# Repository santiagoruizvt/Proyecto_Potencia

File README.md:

# Proyecto_Potencia
Repositorio destinado al proyecto de la materia Electrónica de Potencia

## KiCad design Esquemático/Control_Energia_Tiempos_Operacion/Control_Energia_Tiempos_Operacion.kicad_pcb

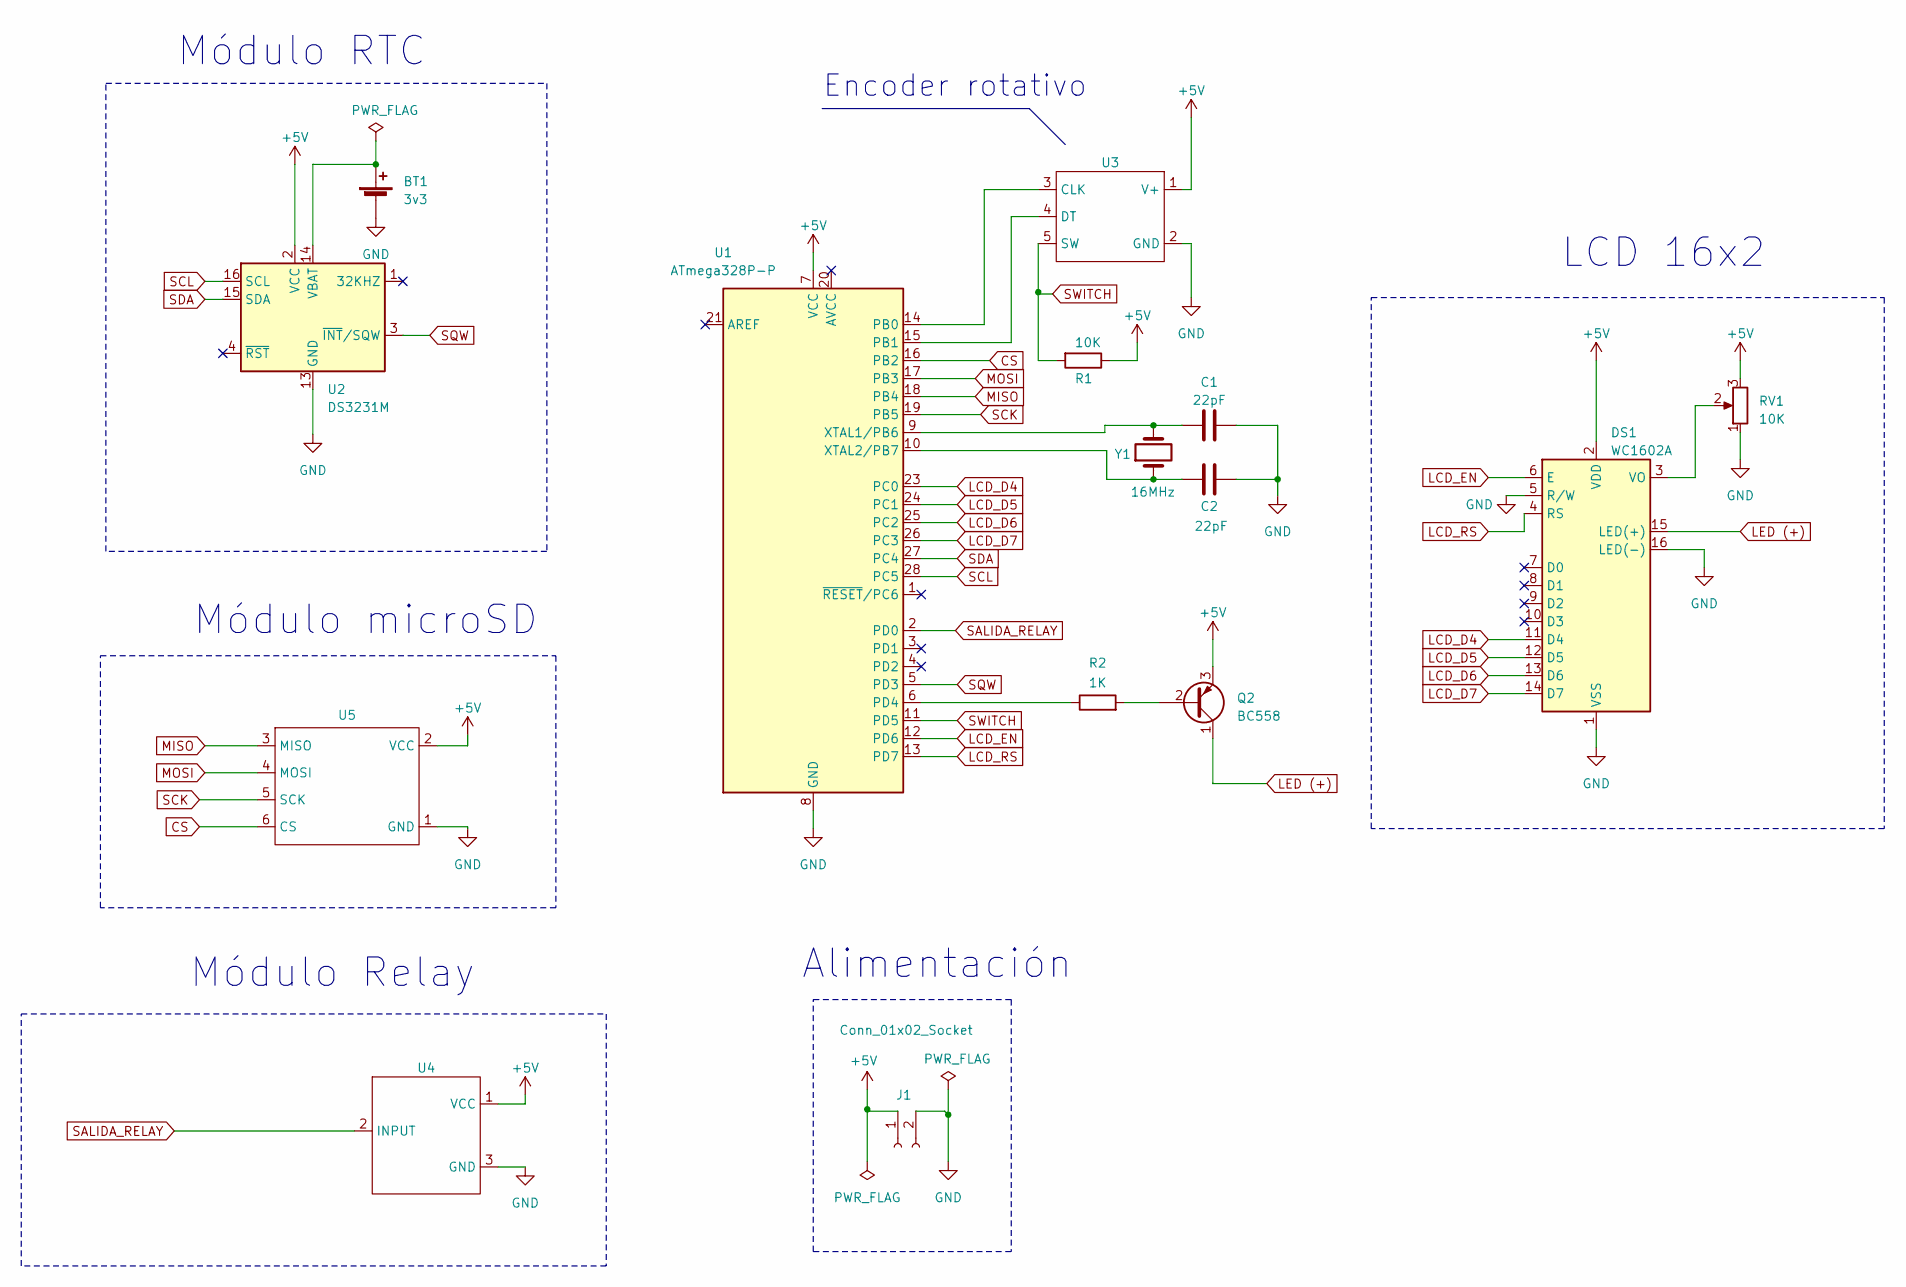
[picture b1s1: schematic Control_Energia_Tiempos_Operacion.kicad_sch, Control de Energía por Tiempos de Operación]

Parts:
BT1: 3v3
C1, C2: 22pF; C_Disc_D5.0mm_W2.5mm_P2.50mm
DS1: WC1602A; IDC-Header_2x06-1MP_P2.54mm_Latch6.5mm_Vertical
J1: Conn_01x02_Socket; TerminalBlock_bornier-2_P5.08mm
Q2: BC558; TO-92_Inline
R1: 10K; R_Axial_DIN0207_L6.3mm_D2.5mm_P10.16mm_Horizontal
R2: 1K; R_Axial_DIN0207_L6.3mm_D2.5mm_P10.16mm_Horizontal
RV1: 10K; Potentiometer_Bourns_3296W_Vertical
U1: ATmega328P-P; DIP-28_W7.62mm
U2: DS3231M; PinSocket_2x04_P2.00mm_Vertical
U3: IDC-Header_2x03_P2.54mm_Vertical
U4: PinSocket_1x03_P2.00mm_Vertical
U5: PinSocket_1x06_P2.00mm_Vertical
Y1: 16MHz; Crystal_HC49-4H_Vertical

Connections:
+5V: DS1.2 (VDD), J1.1, Q2.3 (E), R1.1, RV1.3, U1.7 (VCC), U2.2 (VCC), U3.1 (V+), U4.1 (VCC), U5.2 (VCC)
CS: U1.16 (PB2), U5.6 (CS)
GND: BT1.2 (-), C1.2, C2.2, DS1.1 (VSS), DS1.5 (R/W), DS1.16 (LED(-)), J1.2, RV1.1, U1.8 (GND), U1.22 (GND), U2.5 (GND), U2.6 (GND), U2.7 (GND), U2.8 (GND), U2.9 (GND), U2.10 (GND), U2.11 (GND), U2.12 (GND), U2.13 (GND), U3.2 (GND), U4.3 (GND), U5.1 (GND)
LCD_D4: DS1.11 (D4), U1.23 (PC0)
LCD_D5: DS1.12 (D5), U1.24 (PC1)
LCD_D6: DS1.13 (D6), U1.25 (PC2)
LCD_D7: DS1.14 (D7), U1.26 (PC3)
LCD_EN: DS1.6 (E), U1.12 (PD6)
LCD_RS: DS1.4 (RS), U1.13 (PD7)
LED (+): DS1.15 (LED(+)), Q2.1 (C)
MISO: U1.18 (PB4), U5.3 (MISO)
MOSI: U1.17 (PB3), U5.4 (MOSI)
unnamed: BT1.1 (+), U2.14 (VBAT)
unnamed: DS1.3 (VO), RV1.2
unnamed: Q2.2 (B), R2.2
unnamed: U1.14 (PB0), U3.3 (CLK)
unnamed: U1.15 (PB1), U3.4 (DT)
unnamed: R2.1, U1.6 (PD4)
unnamed: C1.1, U1.9 (XTAL1/PB6), Y1.2
unnamed: C2.1, U1.10 (XTAL2/PB7), Y1.1
SALIDA_RELAY: U1.2 (PD0), U4.2 (INPUT)
SCK: U1.19 (PB5), U5.5 (SCK)
SCL: U1.28 (PC5), U2.16 (SCL)
SDA: U1.27 (PC4), U2.15 (SDA)
SQW: U1.5 (PD3), U2.3 (~INT/SQW)
SWITCH: R1.2, U1.11 (PD5), U3.5 (SW)

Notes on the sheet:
Alimentación
LCD 16x2
Encoder rotativo
Módulo microSD
Módulo RTC
Módulo Relay

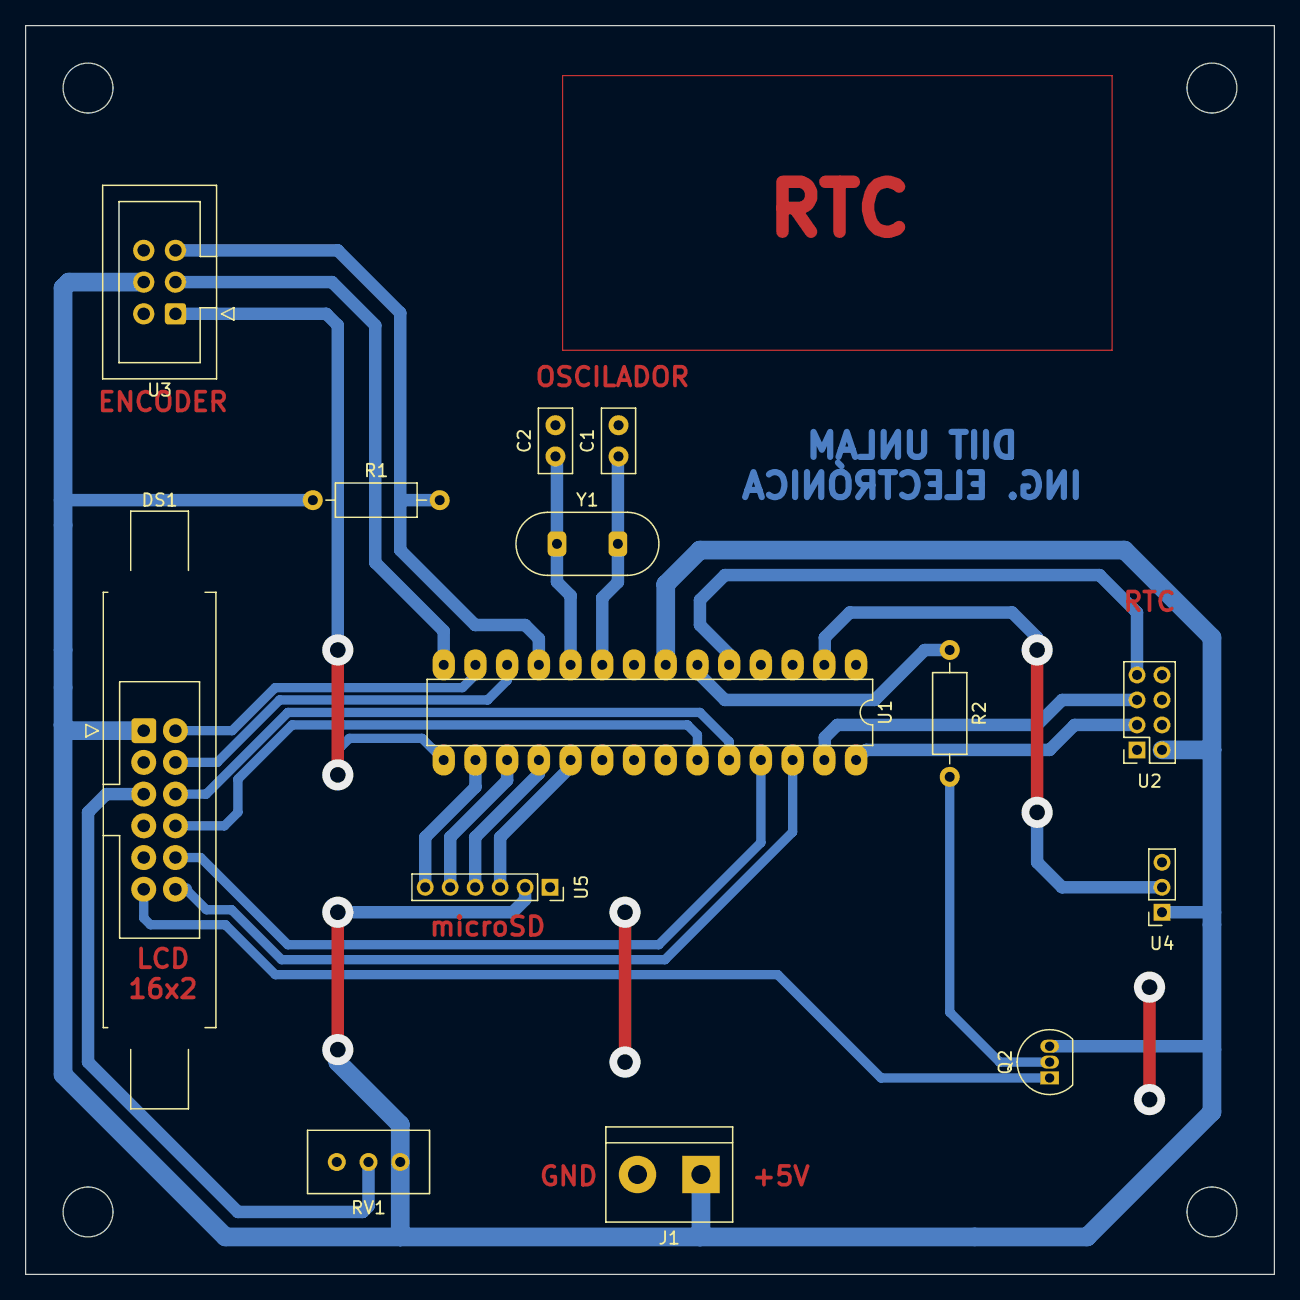
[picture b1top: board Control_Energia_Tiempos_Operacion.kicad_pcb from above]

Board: 2 copper layers, 100.0 x 100.0 mm, 14 parts (0 on the bottom side), 25 nets.

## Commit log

2023-05-18 Agregado del programa inicial. LCD y encoder para seleccionar días
2023-05-18 Corrección encoder.
2023-05-18 Agregado de excel
2023-05-22 Update LCD_Encoder_Dias.ino
    Se agrega el manejo de los distintos menúes, simulando el RTC con un Timer.
2023-05-22 readme
2023-05-23 Se agrega EEPROM - Programación Semanal
    Por ahora la programación semanal acepta cualquier valor. Hay que asegurarse que los encendidos ocurran antes que los apagados y que los rangos no se superpongan (entre otras cosas a detallar).
    Video del funcionamiento:
    https://drive.google.com/file/d/1EcfEMQKbVpGrow3jqm48_inyMvtoU40a/view?usp=share_link
    Guardado de variables en memoria:
    https://docs.google.com/spreadsheets/d/1By1mbL209ivBhk7KslNObIQkLeI79eL5sD7_9IqCB14/edit?usp=sharing
2023-05-24 Agregado de Salida_Rele y encabezados de funciones
    Se usa como salida para relé el pin 13 para ver su estado con el led de la placa del Arduino UNO.
    Se enciende si está dentro de los rangos programados, y se apaga si no lo está.
    Por el momento se deja por defecto que es siempre domingo, hasta agregar las funciones del RTC.
2023-05-24 RTC con interrupciones
2023-05-25 Cambio ubicación de los pines del LCD
    Modificación previa a agregar el módulo RTC para liberar el pin de interrupción.
2023-05-25 Agregado de RTC y validación de fechas
    - Se agrega lectura y grabación del RTC.
    - Se validan las fechas seleccionadas en el Reloj.
    - Se muestra el día de semana en la pantalla principal y en el ajuste de Reloj.
    - Se modifican las posiciones de la memoria para rangos de eventos (arranca en lunes, termina en domingo):
    https://docs.google.com/spreadsheets/d/1By1mbL209ivBhk7KslNObIQkLeI79eL5sD7_9IqCB14/edit?usp=sharing
2023-05-26 Agregado de Menú Feriados
    - Se agrega lectura y grabación de feriados
    - Se agrega #define para el DEBUG_SERIE
2023-05-26 Agregado de README con posibles mejoras
2023-05-27 Se agrega control de backlight del LCD
    Se utiliza el pin 4 como salida para que, si pasa un minuto sin tocar el encoder, se apague el backlight.
2023-05-28 Agregado de pines utilizados en Readme
2023-06-01 Agregado de proyecto de KiCad con circuito esquemático sin uSD
2023-06-01 ERC completo en esquemático
2023-06-06 Feriados en SD
2023-06-11 fix .jar de feriados sd
2023-06-12 Esquemático y PCBs actualizado, incluye uSD
2023-06-12 Corrección PCB
2023-06-19 Update README.md
    Modificaciones en los pines utilizados y agregado de pines para la microSD.
2023-06-19 Lectura/grabación de microSD y más
    Cambios:
    - Se agrega la lectura y grabación de microSD para configurar los feriados.
    - Se cambian las posiciones del relé y del switch del encoder.
    - Se guardan variables en PROGMEM para tener más espacio en el código.
    - Algunas variables globales pasan a ser locales para tener más espacio en el código.
    - Se modifican los buffers fijos de lcd.print o Serial.print para tener más espacio en el código.
2023-06-20 eventos en sd
2023-06-25 lectura sd arduino bugfix eventos
2023-06-25 Se leen los eventos de la microSD
    - Se modifica la lectura de los feriados de la microSD
    - Se agrega la lectura de los eventos de la microSD
    - Se comenta la grabación de los feriados en la microSD hasta agregar también la grabación de los eventos.
2023-06-26 Guarda en la microSD los feriados y eventos
    Se agrega función para que al realizar cualquier cambio desde el dispositivo, regenere el archivo en la microSD (si está colocada) guardando la programación de feriados y eventos.
2023-06-26 Archivo de programación default
    El archivo FERIADOS.txt por default incluye lo siguiente:
    - Setea los feriados del 2023
    - Setea los eventos de la semana en los horarios que se cursa en la facultad
    Lunes a viernes: turno mañana, tarde y noche
    Sabado: turno mañana y tarde
    Domingo: apagado
2023-06-26 Agrego README.md
2023-06-28 Recupera datos SD y formateo de feriados.txt
2023-07-02 formato de eventos con 2 digitos en ambos lados del :
2023-07-03 Se agregan los manuales
    - Elección de microcontrolador
    - Manual de Usuario
    - Manual Técnico (Falta link de video)
2023-07-03 Se agrega código del firmware y sus librerías
2023-07-03 Update control_de_energia.ino
    Modificación para que cuando se cargue la programación por microSD, vuelva a cargar los rangos del día por si se modificaron
2023-07-03 Add files via upload
    Se agrega link de video
2023-07-11 Manual Técnico Rev002
    Se agrega la interpretación del archivo "feriados.txt" de la micro SD
2023-07-11 Actualización de PCB, se pueden corregir algunas huellas para el armado de futuros prototipos.
2023-07-11 Agregado de archivos STLs de la base y tapa
2023-07-11 Corrección de lista de materiales PNP
2023-07-11 Subo el zip enviado por Miel
